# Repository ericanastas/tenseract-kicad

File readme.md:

# Tenseract Kicad

PCBs for Tenseract Burning Man art project

- https://tenseract.art
- https://github.com/ericanastas/tenseract

[Tenseract_JBox.pdf](./Tenseract_JBox.pdf)

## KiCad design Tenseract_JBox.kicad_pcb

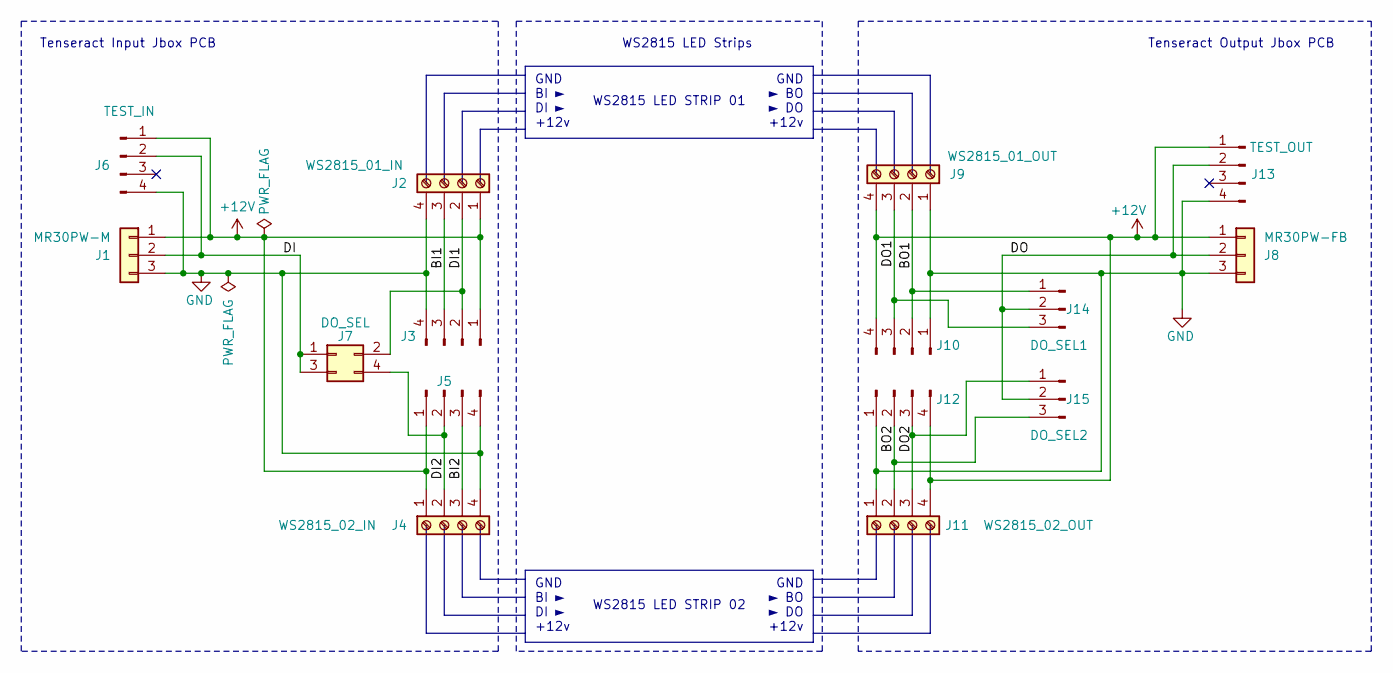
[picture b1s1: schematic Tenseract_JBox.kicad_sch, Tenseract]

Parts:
J1: MR30PW-M; AMASS_MR30PW-M_1x03_P3.50mm_Horizontal
J2: WS2815_01_IN; TerminalBlock_Phoenix_MPT-0,5-4-2.54_1x04_P2.54mm_Horizontal
J3, J5, J10, J12: Conn_01x04_Pin; PinHeader_1x04_P2.54mm_Vertical
J4: WS2815_02_IN; TerminalBlock_Phoenix_MPT-0,5-4-2.54_1x04_P2.54mm_Horizontal
J6: TEST_IN; PinHeader_1x04_P2.54mm_Vertical
J7: DO_SEL; PinHeader_2x02_P2.54mm_Vertical
J8: MR30PW-FB; AMASS_MR30PW-FB_1x03_P3.50mm_Horizontal
J9: WS2815_01_OUT; TerminalBlock_Phoenix_MPT-0,5-4-2.54_1x04_P2.54mm_Horizontal
J11: WS2815_02_OUT; TerminalBlock_Phoenix_MPT-0,5-4-2.54_1x04_P2.54mm_Horizontal
J13: TEST_OUT; PinHeader_1x04_P2.54mm_Vertical
J14: DO_SEL1; PinHeader_1x03_P2.54mm_Vertical
J15: DO_SEL2; PinHeader_1x03_P2.54mm_Vertical

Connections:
+12V: J1.1, J2.1, J3.1, J4.1, J5.1, J6.1, J8.1, J9.4, J10.4, J11.4, J12.4, J13.1
/BI1: J2.3, J3.3
/BI2: J4.3, J5.3
/BO1: J9.2, J10.2, J14.1
/BO2: J11.2, J12.2, J15.3
/DI: J1.2, J6.2, J7.1, J7.3
/DI1: J2.2, J3.2, J7.2
/DI2: J4.2, J5.2, J7.4
/DO: J8.2, J13.2, J14.2, J15.2
/DO1: J9.3, J10.3, J14.3
/DO2: J11.3, J12.3, J15.1
GND: J1.3, J2.4, J3.4, J4.4, J5.4, J6.4, J8.3, J9.1, J10.1, J11.1, J12.1, J13.4

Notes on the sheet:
GND BI ► DI ► +12v
WS2815 LED STRIP 02
Tenseract Input Jbox PCB
WS2815 LED STRIP 01
Tenseract Output Jbox PCB
GND ► BO ► DO +12v
WS2815 LED Strips

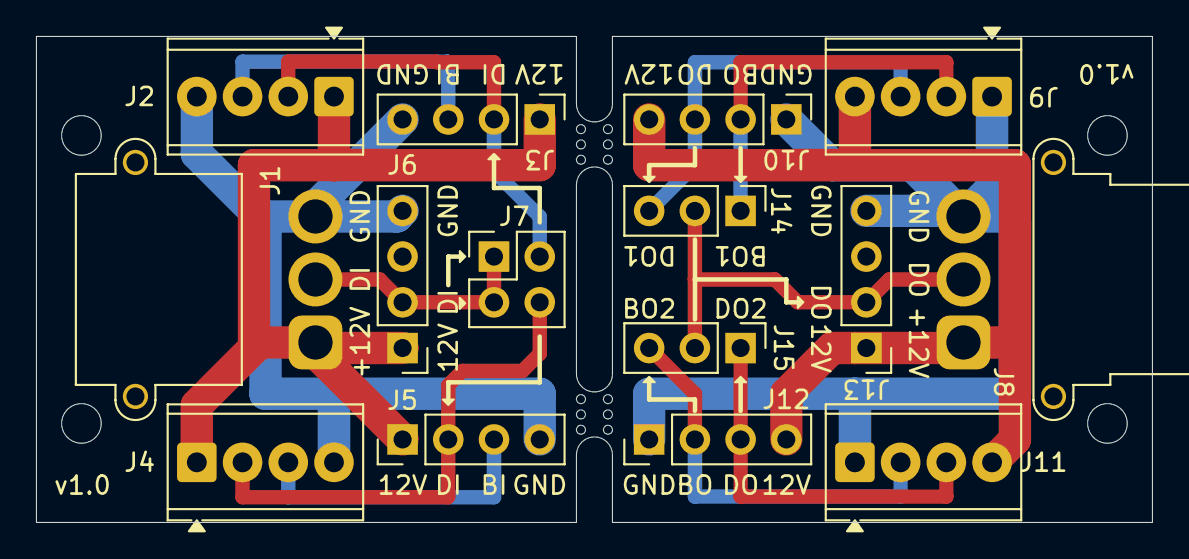
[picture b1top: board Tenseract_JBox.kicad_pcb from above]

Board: 2 copper layers, 62.0 x 27.0 mm, 15 parts (0 on the bottom side), 12 nets.

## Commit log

2026-06-23 Inital commit
2026-06-23 moved mountiong holes in 0.5mm
2026-06-23 Added image and readme
2026-06-23 Updated 3d step model
2026-06-24 Finished 2nd pcb
2026-06-24 Updated image
2026-06-24 Updated step model
2026-06-24 Added grouping boxes to schematic
2026-06-24 Updated schematic formating, set revsion to 1.0
2026-06-24 Created schematic svg and pdf
2026-06-24 Clean up extraneous plot files, moved 3d models into 3d-models folder
2026-06-24 Added strut render
2026-06-24 Added seperate input and output pcb step files
2026-06-24 Fixed mouse bites
2026-06-24 Exported Gerber and drill files
2026-06-24 Removed JLCJLCJLCJLC placeholder
2026-06-25 split input and output pcbs into seperate files
